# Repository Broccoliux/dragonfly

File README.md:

---
 
# Dragonfly
 
A custom all-in-one flight controller + ESC, built entirely from discrete ICs rather than premade modules, designed for me by me. Flight control and all 4 motor drivers live on a single 4-layer PCB, designed from scratch in KiCad.
 
# Why I Built This
 
I wanted to go past just building a flight controller most DIY FC projects stop at a board that reads a gyro and outputs signals. I wanted the whole thing: FC and ESC combined on one board, IC-level design instead of stacking pre-built modules, a custom 3D-printed frame, and firmware configured to actually fly and hold up to real maneuvers, not just hover.
 
This became a fromscratch systems project schematic, PCB layout, mechanical frame design, and firmware, all built and understood end-to-end rather than assembled from a kit.
 
---
     
## Features
 
- 4-layer PCB designed from scratch in KiCad, all-in-one FC + ESC on a single board
- STM32F405RGTx flight controller MCU running Betaflight, custom unified target
- 4x independent ESC channels, each with its own AT32F421G8U7 MCU running AM32 firmware real per-motor commutation, not a single shared driver
- FD6288Q 3-phase gate drivers + discrete MOSFETs per channel, sized for freestyle current draw, not just hover
- ICM-20602 IMU (SPI), isolated placement and routing to minimize motor-noise coupling into gyro data
- AT7456E OSD for FPV video overlay (battery voltage, timer)
- BMP280 barometer for altitude hold
- TPS5430 buck (5V) + AMS1117-3.3 LDO + dedicated L78L08 8V rail for gate drivers — separate, correctly isolated power domains
- Individual SWD test points per ESC channel for one-time AM32 flashing
- ELRS receiver support (Happymodel Nano RX) over UART
- Custom 3" toothpick-class frame, designed in Fusion 360, 3D printed
- **Estimated build cost:** ~$250–300 (board, motors, frame, battery, receiver, transmitter)
---
 
## What's Inside
 
| Component | Part | Specification |
|---|---|---|
| Flight Controller MCU | STM32F405RGTx | ARM Cortex-M4, 168 MHz |
| IMU | ICM-20602 | 6-axis, SPI |
| ESC MCU (x4) | AT32F421G8U7 | One per motor, runs AM32 |
| Gate Driver (x4) | FD6288Q | 3-phase, one per motor |
| Motor Drive | 6x MOSFET per channel | 24 total, sized for real current draw |
| Buck Regulator | TPS5430 | Battery → 5V |
| LDO | AMS1117-3.3 | 5V → 3.3V |
| Gate Driver Supply | L78L08 | Battery → 8V, dedicated rail |
| OSD | AT7456E | Analog FPV video overlay |
| Barometer | BMP280 | Altitude hold |
| Receiver | Happymodel ELRS Nano RX | UART |
| Transmitter | RadioMaster Zorro (ELRS) | Full-size hall gimbals |
| Motors | 3" class, 1404, ~3800–4500KV | 4S |
| Frame | Custom 3" toothpick | 3D printed, Fusion 360 |
| PCB | 4-layer | KiCad |
 
---
 
## Firmware
 
**Status:** in progress configuration and pin-mapping stage, not reqady to flash
 
Two separate firmware bases run on this board:
 
- **Betaflight** (main STM32F405) custom unified target describing this board's exact pin map (motors, IMU SPI, receiver UART)
- **AM32** (each of the 4 AT32F421 ESC MCUs) open-source ESC firmware, flashed individually per channel via dedicated SWD test points
```bash
firmware/
├── betaflight-unified-target/   # Unified target config for the main FC
├── am32/                        # AM32 firmware source, per-channel builds
└── notes.md                     # Pin mapping reference
```
 
---
 
## How to Use
 
### Hardware
 
1. PCB files are located in `PCB/`
2. Open the `.kicad_pro` file in KiCad 8+
3. Upload Gerbers from `PCB/gerbers/` to JLCPCB (4-layer)
4. Order components using `BOM/BOM.csv`
5. Frame STEP file is available in `CAD/`
### Firmware
 
1. Flash AM32 onto each of the 4 ESC MCUs individually, using the SWD test points per channel
2. Flash Betaflight onto the main STM32 via USB-C, using the custom unified target in `firmware/betaflight-unified-target/`
3. Configure IMU calibration, receiver binding, and OSD via Betaflight Configurator
---
 
## Repository Structure
 
```text
Dragonfly/
├── PCB/                         # KiCad project + Gerbers
├── CAD/                         # Fusion 360 frame design (.step)
├── firmware/                    # Betaflight unified target + AM32
├── BOM/                         # Bill of Materials
├── imgs/                        # Photos and renders
└── README.md
```
 
---
 
## Built By
 
**broccoli 🥦** — Solo hardware builder from Pakistan.
 
*Chasing what I love. GE0*

'geo geo geo

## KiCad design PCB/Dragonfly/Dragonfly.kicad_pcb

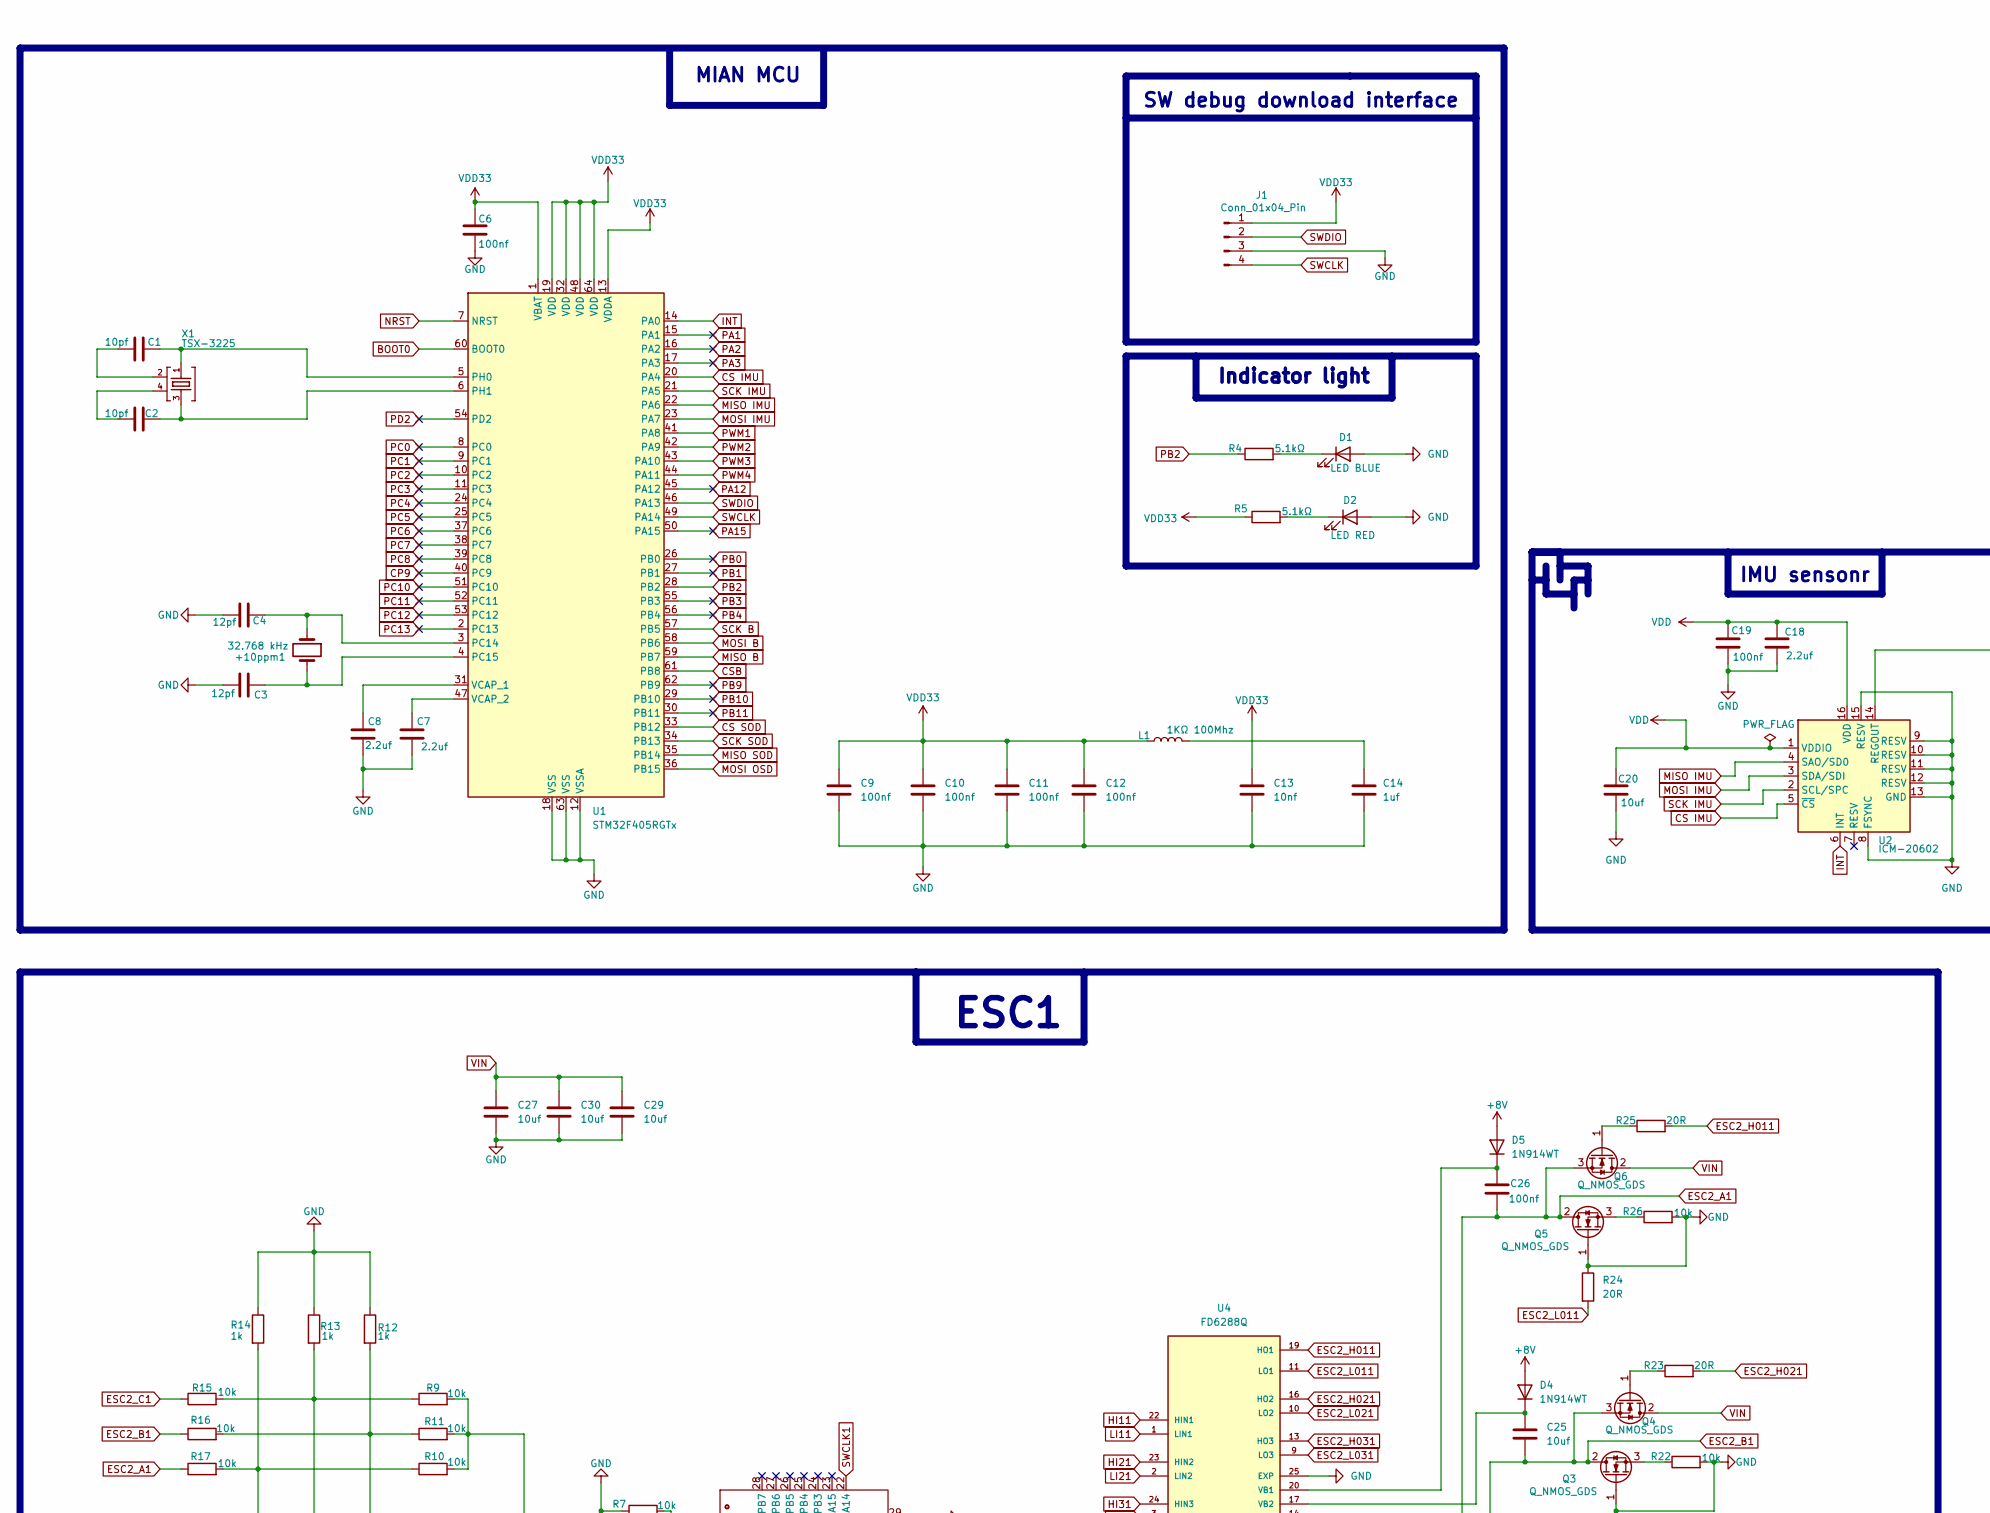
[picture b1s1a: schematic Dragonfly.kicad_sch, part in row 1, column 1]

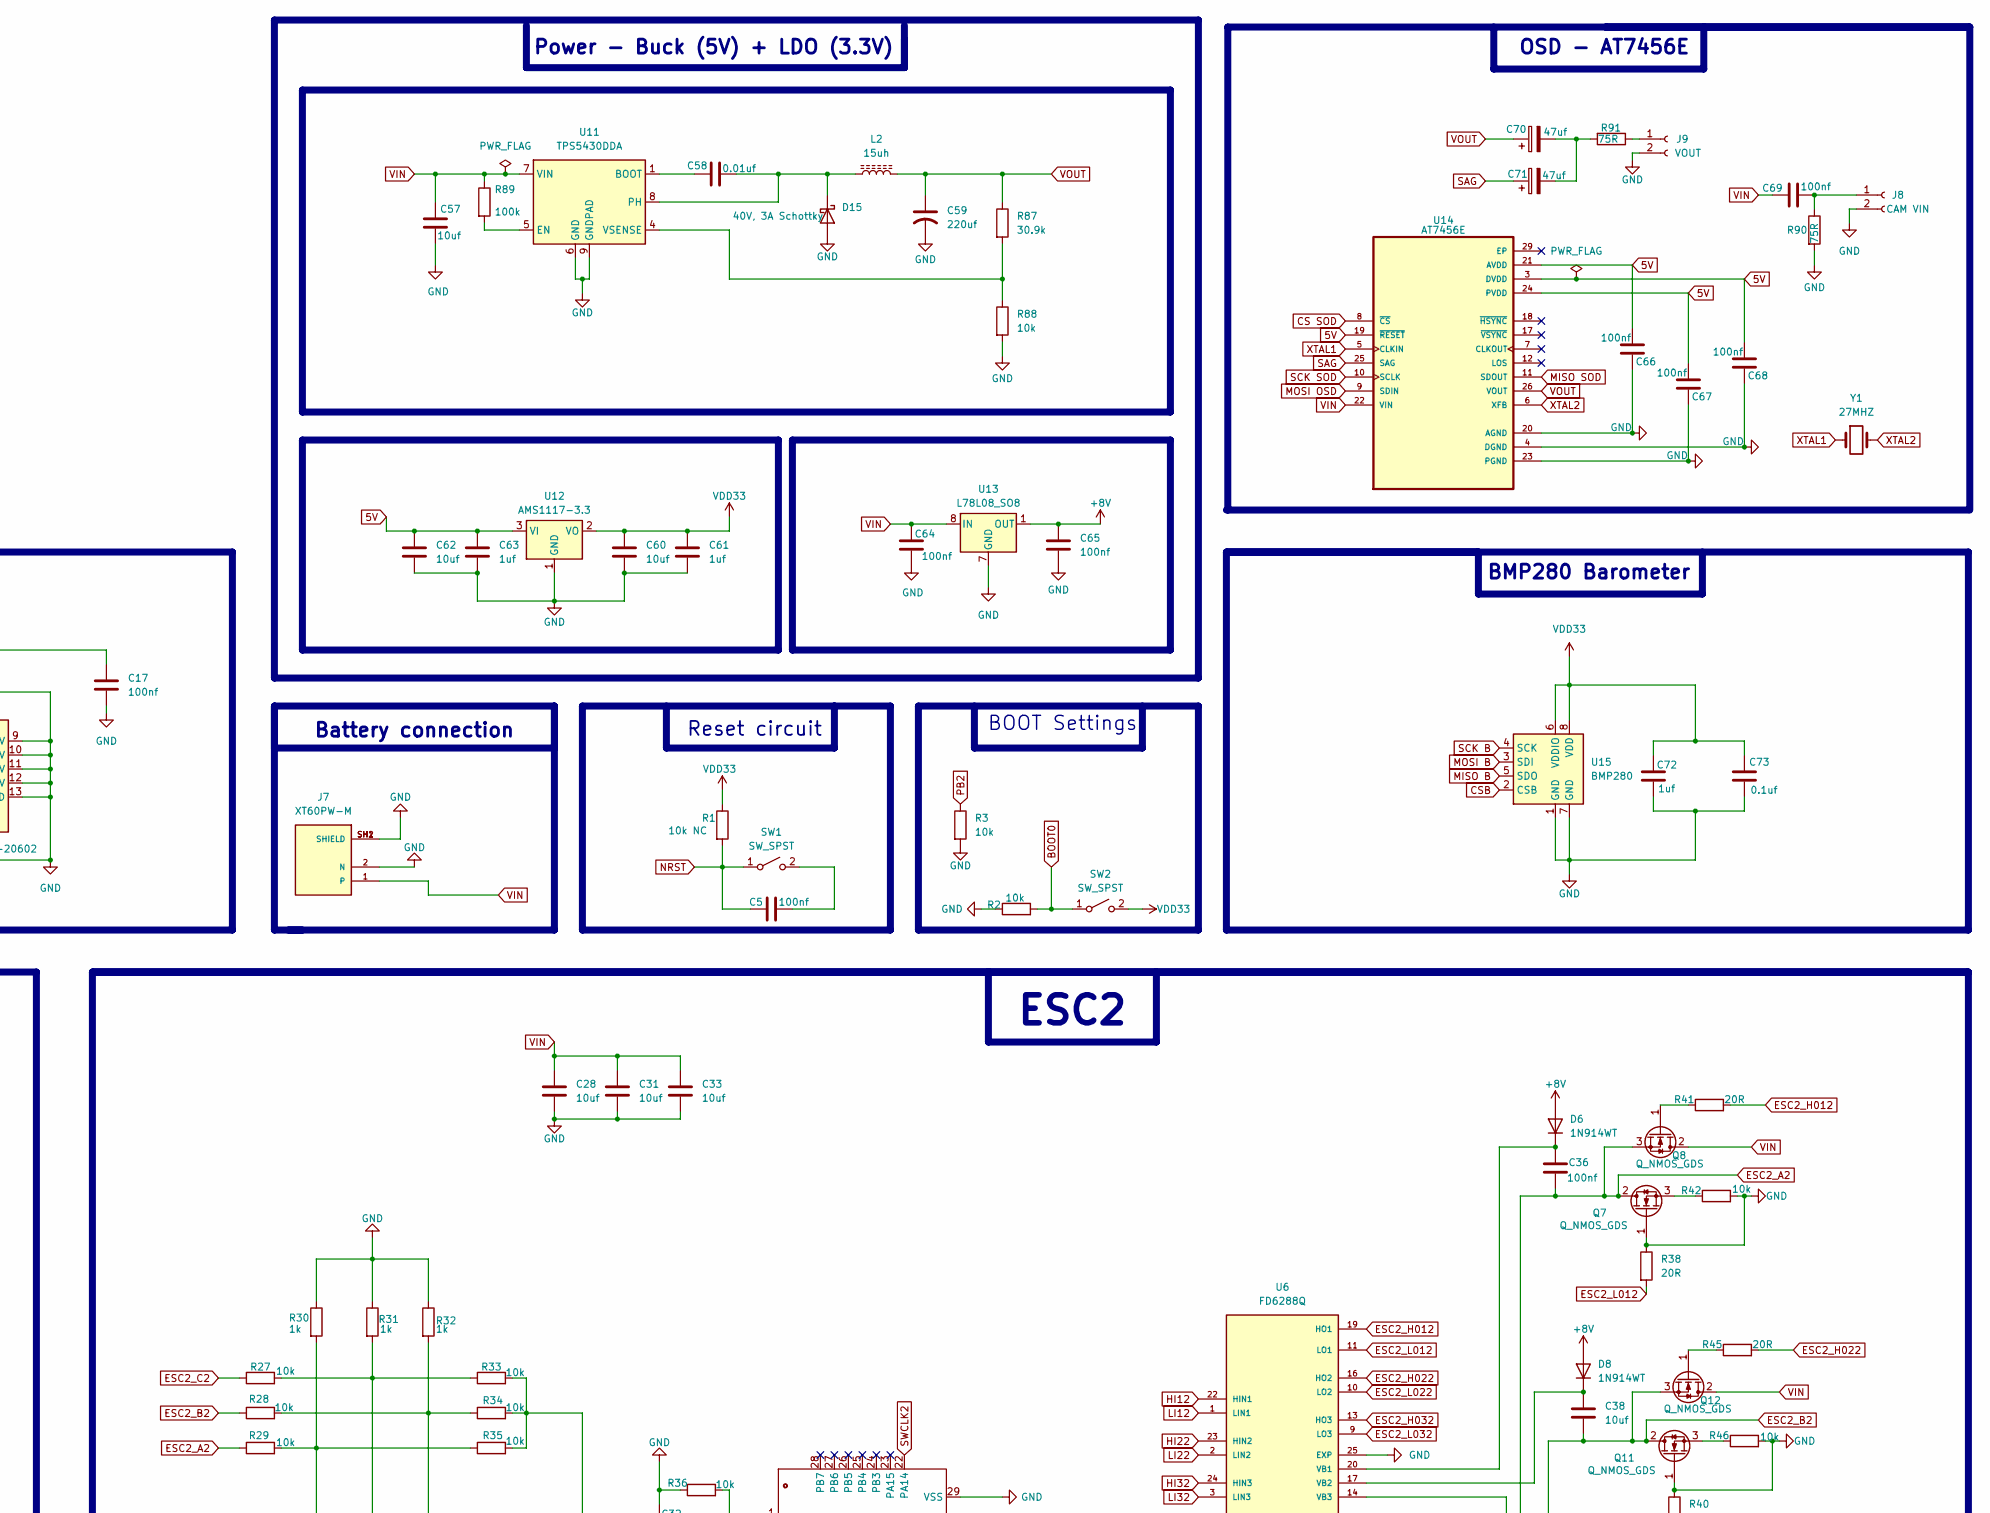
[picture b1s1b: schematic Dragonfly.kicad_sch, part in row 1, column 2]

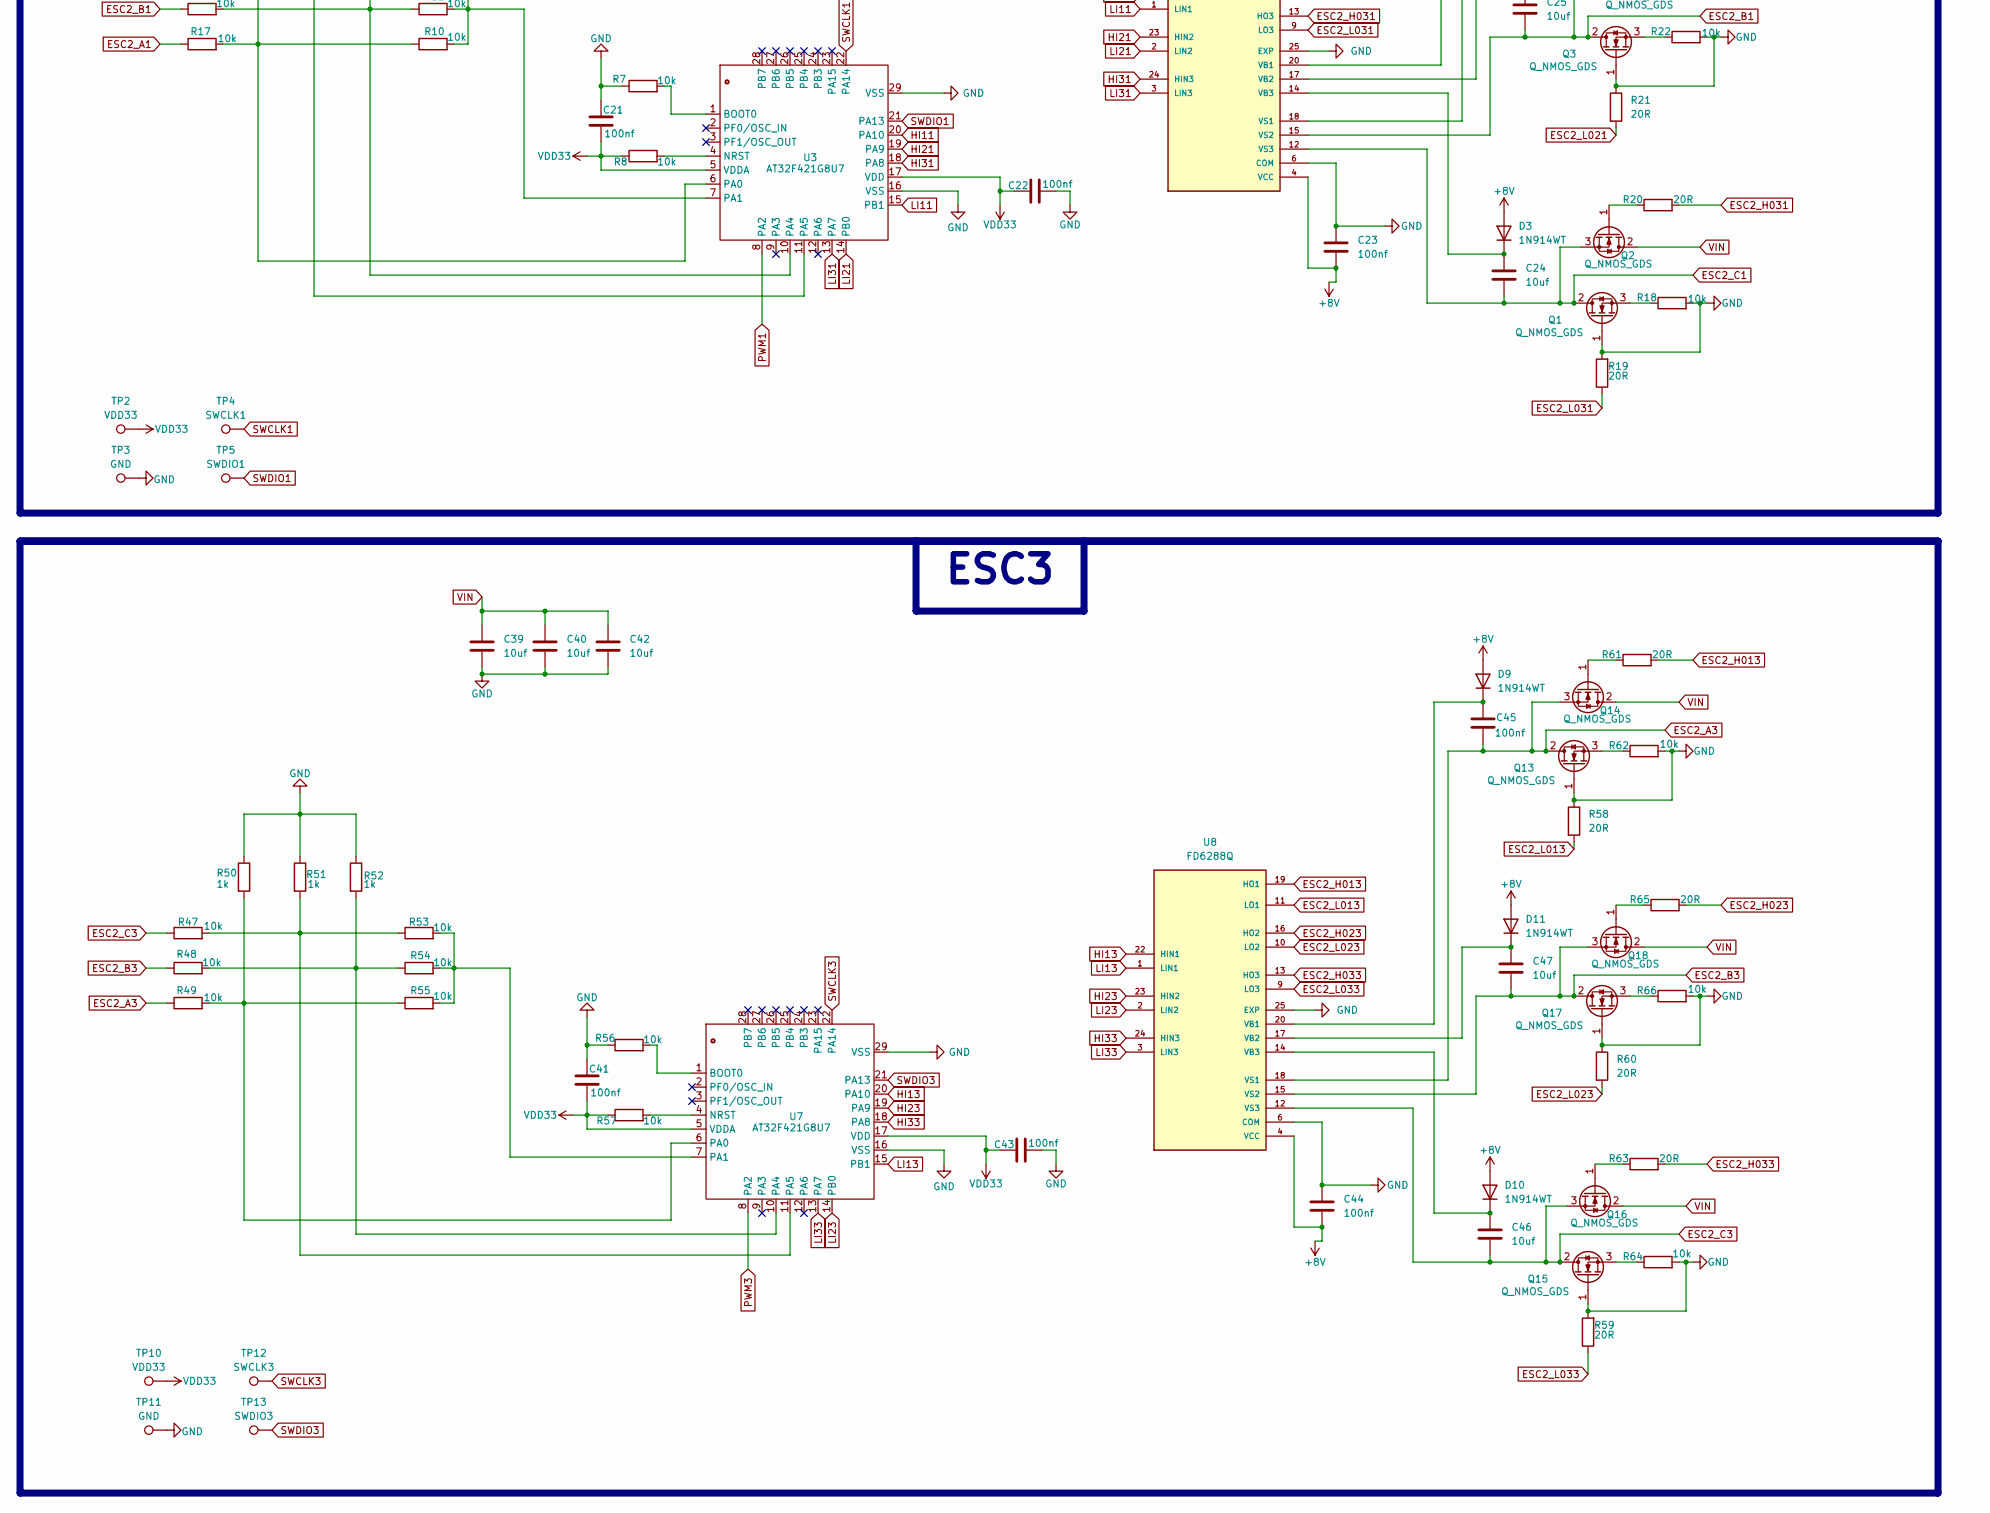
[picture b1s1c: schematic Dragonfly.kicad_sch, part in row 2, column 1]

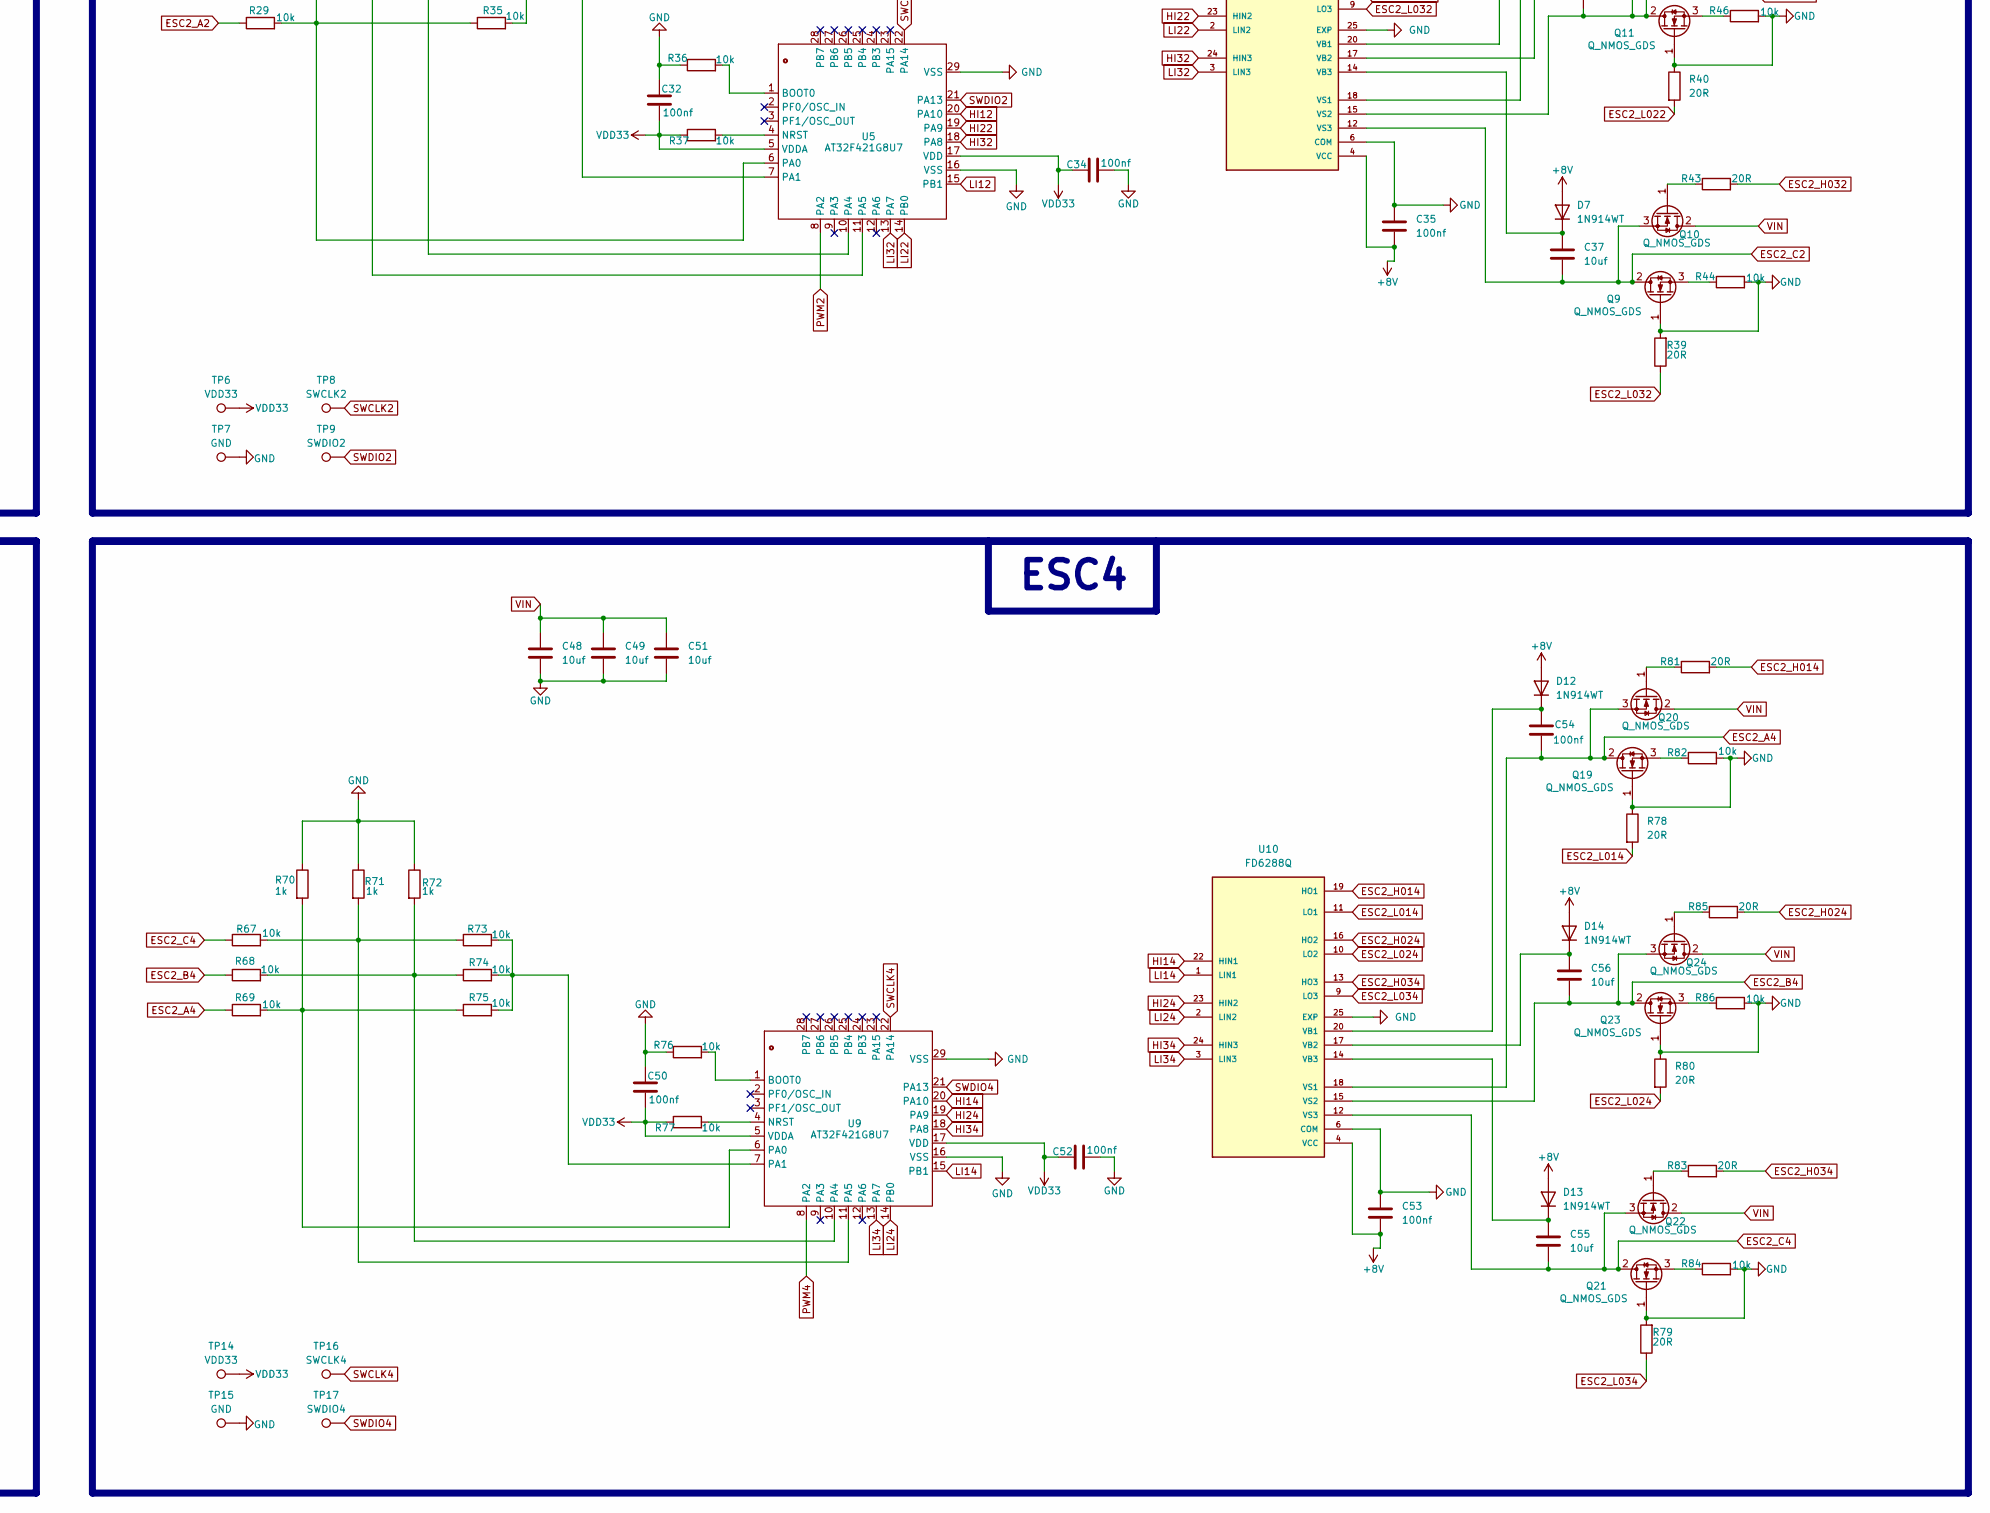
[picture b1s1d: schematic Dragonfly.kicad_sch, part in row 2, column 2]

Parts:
+10ppm1: 32.768 kHz; Crystal_SMD_3225-4Pin_3.2x2.5mm
C1, C2: 10pf; C_0402_1005Metric
C3, C4: 12pf; C_0402_1005Metric
C5, C6, C9, C10, C11, C12, C17, C19, C21, C22, C23, C26, C32, C34, C35, C36, C41, C43, C44, C45, C50, C52, C53, C54, C64, C65, C66, C67, C68, C69: 100nf; C_0402_1005Metric
C7, C8, C18: 2.2uf; C_0402_1005Metric
C13: 10nf; C_0402_1005Metric
C14, C61, C63, C72: 1uf; C_0402_1005Metric
C20, C24, C25, C27, C28, C29, C30, C31, C33, C37, C38, C39, C40, C42, C46, C47, C48, C49, C51, C55, C56, C57, C60, C62: 10uf; C_0402_1005Metric
C58: 0.01uf; C_0402_1005Metric
C59: 220uf; CP_Elec_6.3x5.8
C70, C71: 47uf; C_0402_1005Metric
C73: 0.1uf; C_0402_1005Metric
D1: LED BLUE; LED_0201_0603Metric
D2: LED RED; LED_0201_0603Metric
D3, D4, D5, D6, D7, D8, D9, D10, D11, D12, D13, D14: 1N914WT; D_SOD-523
D15: 40V, 3A Schottky; D_SMC
J1: Conn_01x04_Pin; JST_EH_B4B-EH-A_1x04_P2.50mm_Vertical
J7: XT60PW-M; AMASS_XT60PW-M; PARTREV 1.2
J8: CAM VIN; JST_EH_B2B-EH-A_1x02_P2.50mm_Vertical
J9: VOUT; JST_EH_B2B-EH-A_1x02_P2.50mm_Vertical
L1: 1KΩ 100Mhz; L_0402_1005Metric
L2: 15uh; L_Wurth_WE-LQSH-4020
Q1, Q2, Q3, Q4, Q5, Q6, Q7, Q8, Q9, Q10, Q11, Q12, Q13, Q14, Q15, Q16, Q17, Q18, Q19, Q20, Q21, Q22, Q23, Q24: Q_NMOS_GDS; Diodes_PowerDI3333-8
R1: 10k NC; R_0402_1005Metric
R2, R3, R7, R8, R9, R10, R11, R15, R16, R17, R18, R22, R26, R27, R28, R29, R33, R34, R35, R36, R37, R42, R44, R46, R47, R48, R49, R53, R54, R55, R56, R57, R62, R64, R66, R67, R68, R69, R73, R74, R75, R76, R77, R82, R84, R86, R88: 10k; R_0402_1005Metric
R4, R5: 5.1kΩ; R_0402_1005Metric
R12, R13, R14, R30, R31, R32, R50, R51, R52, R70, R71, R72: 1k; R_0402_1005Metric
R19, R20, R21, R23, R24, R25, R38, R39, R40, R41, R43, R45, R58, R59, R60, R61, R63, R65, R78, R79, R80, R81, R83, R85: 20R; R_0402_1005Metric
R87: 30.9k; R_0815_2038Metric
R89: 100k; R_0402_1005Metric
R90, R91: 75R; R_0402_1005Metric
SW1, SW2: SW_SPST; SW_Tactile_SPST_NO_Straight_CK_PTS636Sx25SMTRLFS
TP2, TP6, TP10, TP14: VDD33; TestPoint_Pad_D1.0mm
TP3, TP7, TP11, TP15: GND; TestPoint_Pad_D1.0mm
TP4: SWCLK1; TestPoint_Pad_D1.0mm
TP5: SWDIO1; TestPoint_Pad_D1.0mm
TP8: SWCLK2; TestPoint_Pad_D1.0mm
TP9: SWDIO2; TestPoint_Pad_D1.0mm
TP12: SWCLK3; TestPoint_Pad_D1.0mm
TP13: SWDIO3; TestPoint_Pad_D1.0mm
TP16: SWCLK4; TestPoint_Pad_D1.0mm
TP17: SWDIO4; TestPoint_Pad_D1.0mm
U1: STM32F405RGTx; LQFP-64_10x10mm_P0.5mm
U2: ICM-20602; LGA-16_3x3mm_P0.5mm_LayoutBorder3x5y
U3, U5, U7, U9: AT32F421G8U7
U4, U6, U8, U10: FD6288Q; QFN50P400X400X90-25N
U11: TPS5430DDA; TI_SO-PowerPAD-8_ThermalVias
U12: AMS1117-3.3; SOT-223-3_TabPin2
U13: L78L08_SO8; SOIC-8_3.9x4.9mm_P1.27mm
U14: AT7456E; SOP65P640X120-29N
U15: BMP280; Bosch_LGA-8_2x2.5mm_P0.65mm_ClockwisePinNumbering
X1: TSX-3225
Y1: 27MHZ; Crystal_SMD_3225-4Pin_3.2x2.5mm

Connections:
5V: C62.1, C63.1, C66.1, C67.1, C68.1, U12.3 (VI), U14.3 (DVDD), U14.19 (~RESET), U14.21 (AVDD), U14.24 (PVDD)
+8V: C23.2, C35.2, C44.2, C53.2, C65.1, D3.2 (A), D4.2 (A), D5.2 (A), D6.2 (A), D7.2 (A), D8.2 (A), D9.2 (A), D10.2 (A), D11.2 (A), D12.2 (A), D13.2 (A), D14.2 (A), U4.4 (VCC), U6.4 (VCC), U8.4 (VCC), U10.4 (VCC), U13.1 (OUT)
BOOT0: R2.2, SW2.1 (A), U1.60 (BOOT0)
CP9: U1.40 (PC9)
CS IMU: U1.20 (PA4), U2.5 (~CS)
CS SOD: U1.33 (PB12), U14.8 (~CS)
CSB: U1.61 (PB8), U15.2 (CSB)
ESC2_A1: C26.2, Q5.2 (D), Q6.3 (S), R17.1, U4.18 (VS1)
ESC2_A2: C36.2, Q7.2 (D), Q8.3 (S), R29.1, U6.18 (VS1)
ESC2_A3: C45.2, Q13.2 (D), Q14.3 (S), R49.1, U8.18 (VS1)
ESC2_A4: C54.2, Q19.2 (D), Q20.3 (S), R69.1, U10.18 (VS1)
ESC2_B1: C25.2, Q3.2 (D), Q4.3 (S), R16.1, U4.15 (VS2)
ESC2_B2: C38.2, Q11.2 (D), Q12.3 (S), R28.1, U6.15 (VS2)
ESC2_B3: C47.2, Q17.2 (D), Q18.3 (S), R48.1, U8.15 (VS2)
ESC2_B4: C56.2, Q23.2 (D), Q24.3 (S), R68.1, U10.15 (VS2)
ESC2_C1: C24.2, Q1.2 (D), Q2.3 (S), R15.1, U4.12 (VS3)
ESC2_C2: C37.2, Q9.2 (D), Q10.3 (S), R27.1, U6.12 (VS3)
ESC2_C3: C46.2, Q15.2 (D), Q16.3 (S), R47.1, U8.12 (VS3)
ESC2_C4: C55.2, Q21.2 (D), Q22.3 (S), R67.1, U10.12 (VS3)
ESC2_H011: R25.2, U4.19 (HO1)
ESC2_H012: R41.2, U6.19 (HO1)
ESC2_H013: R61.2, U8.19 (HO1)
ESC2_H014: R81.2, U10.19 (HO1)
ESC2_H021: R23.2, U4.16 (HO2)
ESC2_H022: R45.2, U6.16 (HO2)
ESC2_H023: R65.2, U8.16 (HO2)
ESC2_H024: R85.2, U10.16 (HO2)
ESC2_H031: R20.2, U4.13 (HO3)
ESC2_H032: R43.2, U6.13 (HO3)
ESC2_H033: R63.2, U8.13 (HO3)
ESC2_H034: R83.2, U10.13 (HO3)
ESC2_L011: R24.2, U4.11 (LO1)
ESC2_L012: R38.2, U6.11 (LO1)
ESC2_L013: R58.2, U8.11 (LO1)
ESC2_L014: R78.2, U10.11 (LO1)
ESC2_L021: R21.2, U4.10 (LO2)
ESC2_L022: R40.2, U6.10 (LO2)
ESC2_L023: R60.2, U8.10 (LO2)
ESC2_L024: R80.2, U10.10 (LO2)
ESC2_L031: R19.1, U4.9 (LO3)
ESC2_L032: R39.1, U6.9 (LO3)
ESC2_L033: R59.1, U8.9 (LO3)
ESC2_L034: R79.1, U10.9 (LO3)
GND: C3.2, C4.2, C6.2, C7.2, C8.2, C9.2, C10.2, C11.2, C12.2, C13.2, C14.2, C17.2, C18.2, C19.2, C20.2, C21.1, C22.2, C23.1, C27.2, C28.2, C29.2, C30.2, C31.2, C32.1, C33.2, C34.2, C35.1, C39.2, C40.2, C41.1, C42.2, C43.2, C44.1, C48.2, C49.2, C50.1, C51.2, C52.2, C53.1, C57.2, C59.2, C60.2, C61.2, C62.2, C63.2, C64.2, C65.2, C66.2, C67.2, C68.2, C72.2, C73.2, D1.2 (A), D2.2 (A), D15.2 (A), J1.3, J7.2 (N), J7.SH1 (SHIELD), J7.SH2 (SHIELD), J8.2, J9.2, Q1.1 (G), Q3.1 (G), Q5.1 (G), Q7.1 (G), Q9.1 (G), Q11.1 (G), Q13.1 (G), Q15.1 (G), Q17.1 (G), Q19.1 (G), Q21.1 (G), Q23.1 (G), R2.1, R3.2, R7.1, R12.1, R13.1, R14.1, R18.2, R19.2, R21.1, R22.2, R24.1, R26.2, R30.1, R31.1, R32.1, R36.1, R38.1, R39.2, R40.1, R42.2, R44.2, R46.2, R50.1, R51.1, R52.1, R56.1, R58.1, R59.2, R60.1, R62.2, R64.2, R66.2, R70.1, R71.1, R72.1, R76.1, R78.1, R79.2, R80.1, R82.2, R84.2, R86.2, R88.2, R90.2, TP3.1 (1_1), TP7.1 (1_1), TP11.1 (1_1), TP15.1 (1_1), U1.12 (VSSA), U1.18 (VSS), U1.63 (VSS), U2.8 (FSYNC), U2.9 (RESV), U2.10 (RESV), U2.11 (RESV), U2.12 (RESV), U2.13 (GND), U2.15 (RESV), U3.16 (VSS), U3.29 (VSS), U4.6 (COM), U4.25 (EXP), U5.16 (VSS), U5.29 (VSS), U6.6 (COM), U6.25 (EXP), U7.16 (VSS), U7.29 (VSS), U8.6 (COM), U8.25 (EXP), U9.16 (VSS), U9.29 (VSS), U10.6 (COM), U10.25 (EXP), U11.6 (GND), U11.9 (GNDPAD), U12.1 (GND), U13.2 (GND), U13.3 (GND), U13.6 (GND), U13.7 (GND), U14.4 (DGND), U14.20 (AGND), U14.23 (PGND), U15.1 (GND), U15.7 (GND)
HI11: U3.20 (PA10), U4.22 (HIN1)
HI12: U5.20 (PA10), U6.22 (HIN1)
HI13: U7.20 (PA10), U8.22 (HIN1)
HI14: U9.20 (PA10), U10.22 (HIN1)
HI21: U3.19 (PA9), U4.23 (HIN2)
HI22: U5.19 (PA9), U6.23 (HIN2)
HI23: U7.19 (PA9), U8.23 (HIN2)
HI24: U9.19 (PA9), U10.23 (HIN2)
HI31: U3.18 (PA8), U4.24 (HIN3)
HI32: U5.18 (PA8), U6.24 (HIN3)
HI33: U7.18 (PA8), U8.24 (HIN3)
HI34: U9.18 (PA8), U10.24 (HIN3)
INT: U1.14 (PA0), U2.6 (INT)
LI11: U3.15 (PB1), U4.1 (LIN1)
LI12: U5.15 (PB1), U6.1 (LIN1)
LI13: U7.15 (PB1), U8.1 (LIN1)
LI14: U9.15 (PB1), U10.1 (LIN1)
LI21: U3.14 (PB0), U4.2 (LIN2)
LI22: U5.14 (PB0), U6.2 (LIN2)
LI23: U7.14 (PB0), U8.2 (LIN2)
LI24: U9.14 (PB0), U10.2 (LIN2)
LI31: U3.13 (PA7), U4.3 (LIN3)
LI32: U5.13 (PA7), U6.3 (LIN3)
LI33: U7.13 (PA7), U8.3 (LIN3)
LI34: U9.13 (PA7), U10.3 (LIN3)
MISO B: U1.59 (PB7), U15.5 (SDO)
MISO IMU: U1.22 (PA6), U2.4 (SAO/SD0)
MISO SOD: U1.35 (PB14), U14.11 (SDOUT)
MOSI B: U1.58 (PB6), U15.3 (SDI)
MOSI IMU: U1.23 (PA7), U2.3 (SDA/SDI)
MOSI OSD: U1.36 (PB15), U14.9 (SDIN)
NRST: C5.1, R1.2, SW1.1 (A), U1.7 (NRST)
unnamed: C1.1, X1.2
unnamed: C2.1, X1.4
unnamed: C14.1, L1.2
unnamed: C70.2, C71.2, R91.2
unnamed: D1.1 (K), R4.2
unnamed: D2.1 (K), R5.2
unnamed: C24.1, D3.1 (K), U4.14 (VB3)
unnamed: C25.1, D4.1 (K), U4.17 (VB2)
unnamed: C26.1, D5.1 (K), U4.20 (VB1)
unnamed: C36.1, D6.1 (K), U6.20 (VB1)
unnamed: C37.1, D7.1 (K), U6.14 (VB3)
unnamed: C38.1, D8.1 (K), U6.17 (VB2)
unnamed: C45.1, D9.1 (K), U8.20 (VB1)
unnamed: C46.1, D10.1 (K), U8.14 (VB3)
unnamed: C47.1, D11.1 (K), U8.17 (VB2)
unnamed: C54.1, D12.1 (K), U10.20 (VB1)
unnamed: C55.1, D13.1 (K), U10.14 (VB3)
unnamed: C56.1, D14.1 (K), U10.17 (VB2)
unnamed: C58.2, D15.1 (K), L2.1, U11.8 (PH)
unnamed: C69.2, J8.1, R90.1
unnamed: J9.1, R91.1
unnamed: Q1.3 (S), R18.1
unnamed: Q2.1 (G), R20.1
unnamed: Q3.3 (S), R22.1
unnamed: Q4.1 (G), R23.1
unnamed: Q5.3 (S), R26.1
unnamed: Q6.1 (G), R25.1
unnamed: Q7.3 (S), R42.1
unnamed: Q8.1 (G), R41.1
unnamed: Q9.3 (S), R44.1
unnamed: Q10.1 (G), R43.1
unnamed: Q11.3 (S), R46.1
unnamed: Q12.1 (G), R45.1
unnamed: Q13.3 (S), R62.1
unnamed: Q14.1 (G), R61.1
unnamed: Q15.3 (S), R64.1
unnamed: Q16.1 (G), R63.1
unnamed: Q17.3 (S), R66.1
unnamed: Q18.1 (G), R65.1
unnamed: Q19.3 (S), R82.1
unnamed: Q20.1 (G), R81.1
unnamed: Q21.3 (S), R84.1
unnamed: Q22.1 (G), R83.1
unnamed: Q23.3 (S), R86.1
unnamed: Q24.1 (G), R85.1
unnamed: C5.2, SW1.2 (B)
unnamed: +10ppm1.1, C4.1, U1.3 (PC14)
unnamed: +10ppm1.2, C3.1, U1.4 (PC15)
unnamed: C1.2, U1.5 (PH0), X1.1
unnamed: C2.2, U1.6 (PH1), X1.3
unnamed: C8.1, U1.31 (VCAP_1)
unnamed: C7.1, U1.47 (VCAP_2)
unnamed: C17.1, U2.14 (REGOUT)
unnamed: R7.2, U3.1 (BOOT0)
unnamed: R8.2, U3.4 (NRST)
unnamed: R10.1, R14.2, R17.2, U3.6 (PA0)
unnamed: R9.2, R10.2, R11.2, U3.7 (PA1)
unnamed: R11.1, R12.2, R16.2, U3.10 (PA4)
unnamed: R9.1, R13.2, R15.2, U3.11 (PA5)
unnamed: R36.2, U5.1 (BOOT0)
unnamed: R37.2, U5.4 (NRST)
unnamed: R29.2, R30.2, R35.1, U5.6 (PA0)
unnamed: R33.2, R34.2, R35.2, U5.7 (PA1)
unnamed: R28.2, R32.2, R34.1, U5.10 (PA4)
unnamed: R27.2, R31.2, R33.1, U5.11 (PA5)
unnamed: R56.2, U7.1 (BOOT0)
unnamed: R57.2, U7.4 (NRST)
unnamed: R49.2, R50.2, R55.1, U7.6 (PA0)
unnamed: R53.2, R54.2, R55.2, U7.7 (PA1)
unnamed: R48.2, R52.2, R54.1, U7.10 (PA4)
unnamed: R47.2, R51.2, R53.1, U7.11 (PA5)
unnamed: R76.2, U9.1 (BOOT0)
unnamed: R77.2, U9.4 (NRST)
unnamed: R69.2, R70.2, R75.1, U9.6 (PA0)
unnamed: R73.2, R74.2, R75.2, U9.7 (PA1)
unnamed: R68.2, R72.2, R74.1, U9.10 (PA4)
unnamed: R67.2, R71.2, R73.1, U9.11 (PA5)
unnamed: C58.1, U11.1 (BOOT)
unnamed: R89.2, U11.5 (EN)
unnamed: R87.2, R88.1, U11.4 (VSENSE)
PA1: U1.15 (PA1)
PA2: U1.16 (PA2)
PA3: U1.17 (PA3)
PA12: U1.45 (PA12)
PA15: U1.50 (PA15)
PB0: U1.26 (PB0)
PB1: U1.27 (PB1)
PB2: R3.1, R4.1, U1.28 (PB2)
PB3: U1.55 (PB3)
PB4: U1.56 (PB4)
PB9: U1.62 (PB9)
PB10: U1.29 (PB10)
PB11: U1.30 (PB11)
PC0: U1.8 (PC0)
PC1: U1.9 (PC1)
PC2: U1.10 (PC2)
PC3: U1.11 (PC3)
PC4: U1.24 (PC4)
PC5: U1.25 (PC5)
PC6: U1.37 (PC6)
PC7: U1.38 (PC7)
PC8: U1.39 (PC8)
PC10: U1.51 (PC10)
PC11: U1.52 (PC11)
PC12: U1.53 (PC12)
PC13: U1.2 (PC13)
PD2: U1.54 (PD2)
PWM1: U1.41 (PA8), U3.8 (PA2)
PWM2: U1.42 (PA9), U5.8 (PA2)
PWM3: U1.43 (PA10), U7.8 (PA2)
PWM4: U1.44 (PA11), U9.8 (PA2)
SAG: C71.1, U14.25 (SAG)
SCK B: U1.57 (PB5), U15.4 (SCK)
SCK IMU: U1.21 (PA5), U2.2 (SCL/SPC)
SCK SOD: U1.34 (PB13), U14.10 (SCLK)
SWCLK: J1.4, U1.49 (PA14)
SWCLK1: TP4.1 (1_1), U3.22 (PA14)
SWCLK2: TP8.1 (1_1), U5.22 (PA14)
SWCLK3: TP12.1 (1_1), U7.22 (PA14)
SWCLK4: TP16.1 (1_1), U9.22 (PA14)
SWDIO: J1.2, U1.46 (PA13)
SWDIO1: TP5.1 (1_1), U3.21 (PA13)
SWDIO2: TP9.1 (1_1), U5.21 (PA13)
SWDIO3: TP13.1 (1_1), U7.21 (PA13)
SWDIO4: TP17.1 (1_1), U9.21 (PA13)
VDD: C18.1, C19.1, C20.1, U2.1 (VDDIO), U2.16 (VDD)
VDD33: C6.1, C9.1, C10.1, C11.1, C12.1, C13.1, C21.2, C22.1, C32.2, C34.1, C41.2, C43.1, C50.2, C52.1, C60.1, C61.1, C72.1, C73.1, J1.1, L1.1, R1.1, R5.1, R8.1, R37.1, R57.1, R77.1, SW2.2 (B), TP2.1 (1_1), TP6.1 (1_1), TP10.1 (1_1), TP14.1 (1_1), U1.1 (VBAT), U1.13 (VDDA), U1.19 (VDD), U1.32 (VDD), U1.48 (VDD), U1.64 (VDD), U3.5 (VDDA), U3.17 (VDD), U5.5 (VDDA), U5.17 (VDD), U7.5 (VDDA), U7.17 (VDD), U9.5 (VDDA), U9.17 (VDD), U12.2 (VO), U15.6 (VDDIO), U15.8 (VDD)
VIN: C27.1, C28.1, C29.1, C30.1, C31.1, C33.1, C39.1, C40.1, C42.1, C48.1, C49.1, C51.1, C57.1, C64.1, C69.1, J7.1, Q2.2 (D), Q4.2 (D), Q6.2 (D), Q8.2 (D), Q10.2 (D), Q12.2 (D), Q14.2 (D), Q16.2 (D), Q18.2 (D), Q20.2 (D), Q22.2 (D), Q24.2 (D), R89.1, U11.7 (VIN), U13.8 (IN), U14.22 (VIN)
VOUT: C59.1, C70.1, L2.2, R87.1, U14.26 (VOUT)
XTAL1: U14.5 (CLKIN), Y1.1
XTAL2: U14.6 (XFB), Y1.2

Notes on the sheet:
Indicator light
Reset circuit
BMP280 Barometer
ESC1
Battery connection
ESC4
OSD - AT7456E
BOOT Settings
ESC3
Power - Buck (5V) + LDO (3.3V)
SW debug download interface
ESC2
IMU sensonr
MIAN MCU

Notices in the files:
README.md:
License: MIT
